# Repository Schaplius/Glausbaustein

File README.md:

# Glausbaustein
Einfache glasbausteinlampe mit steuerbaren leds und einem 3D-gedrucktem Gehäuse

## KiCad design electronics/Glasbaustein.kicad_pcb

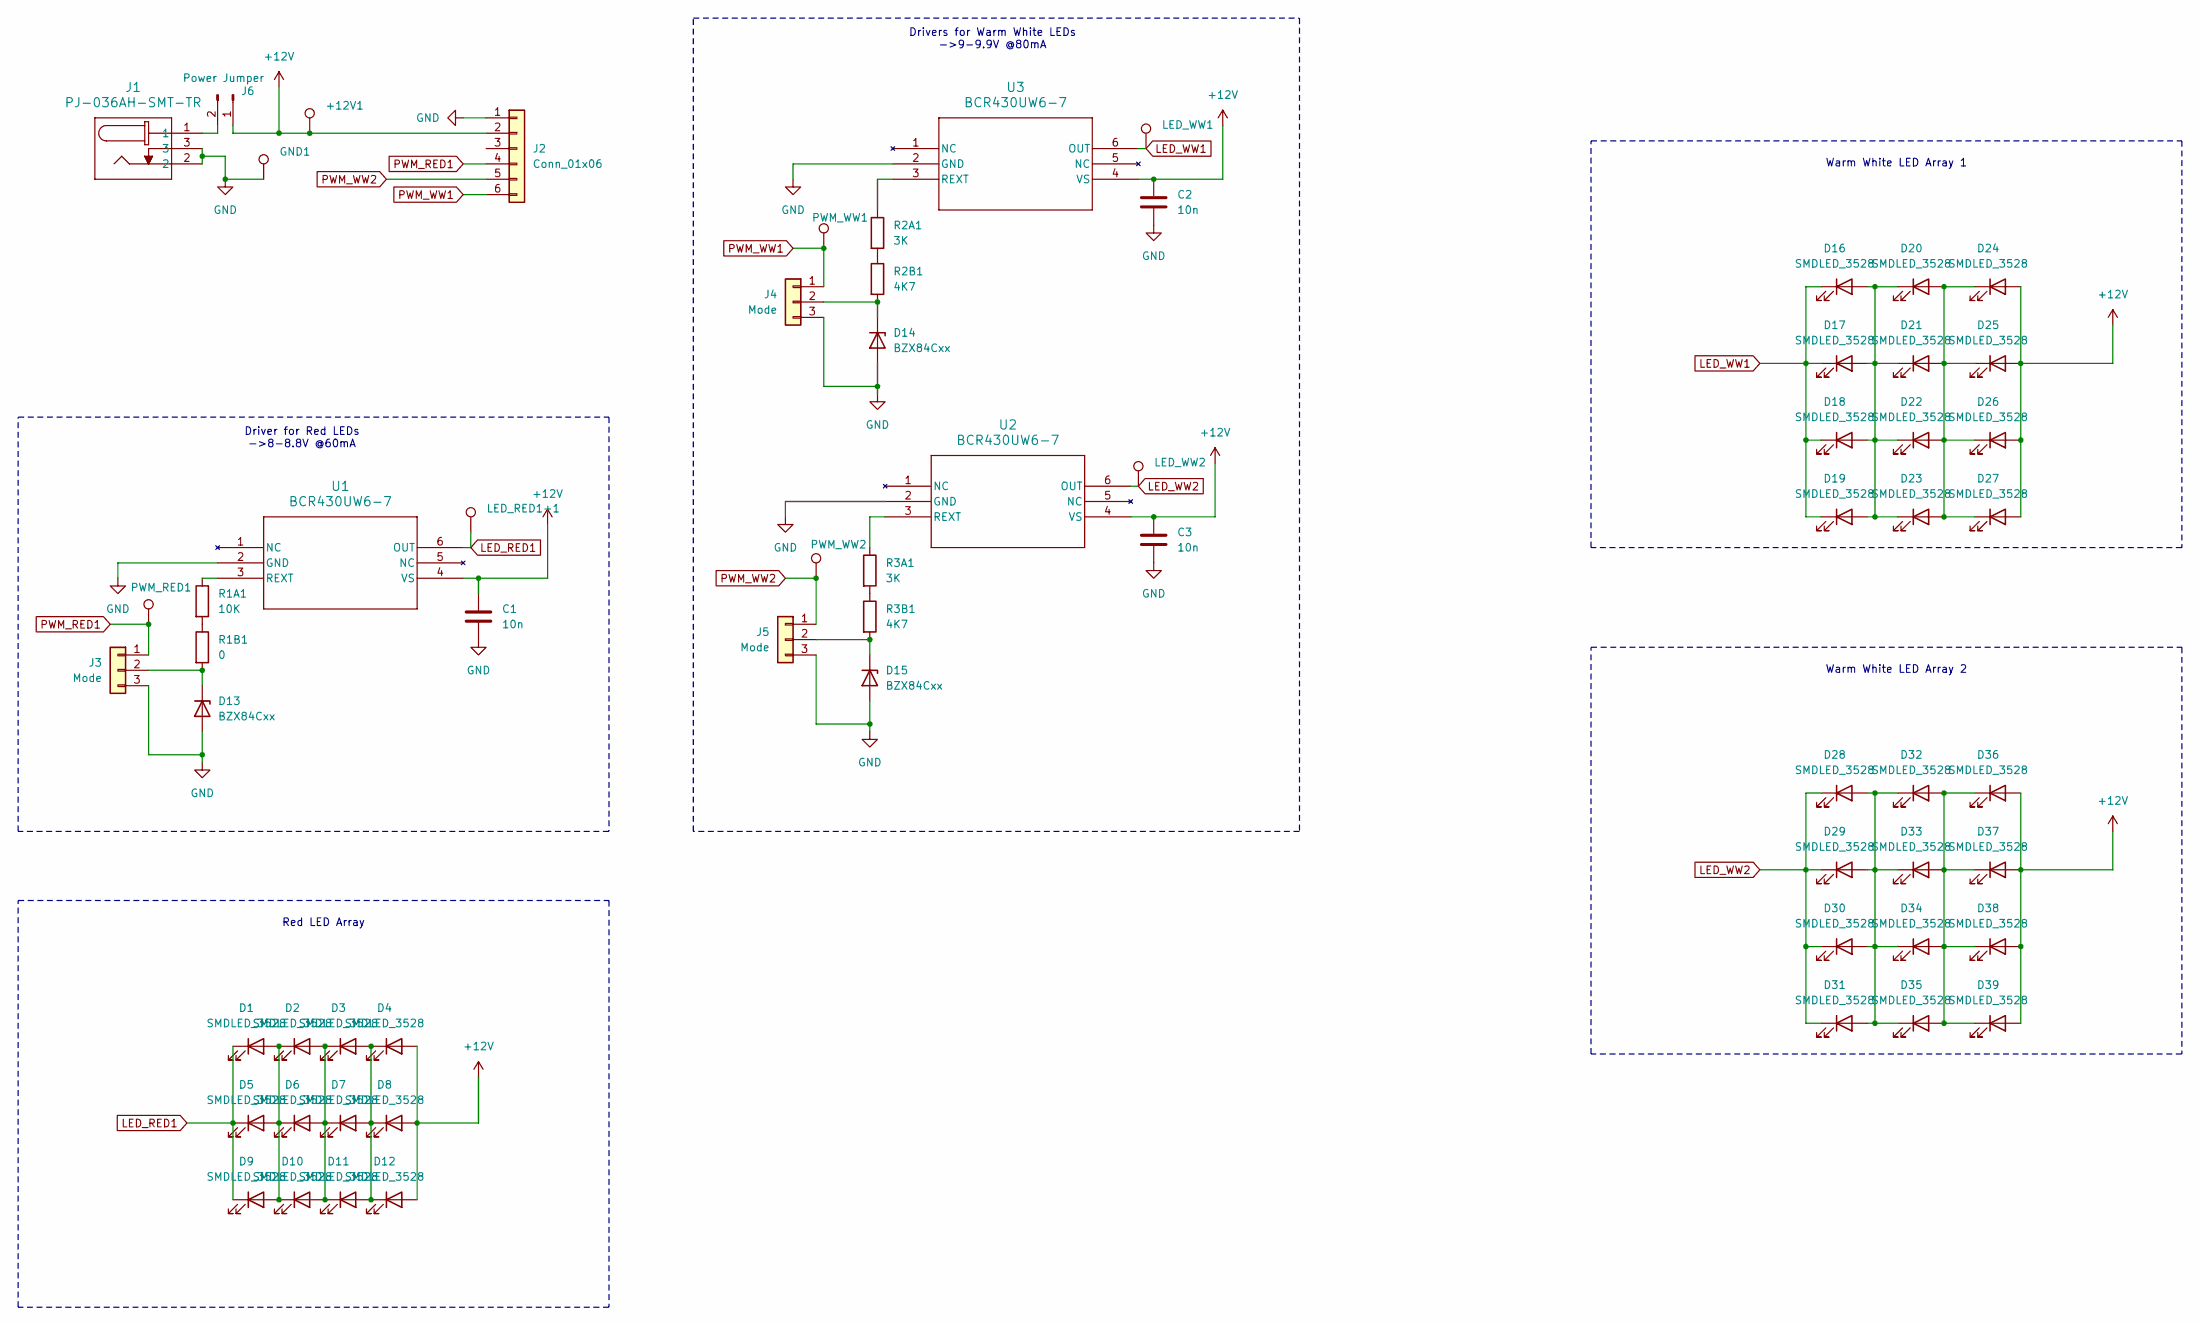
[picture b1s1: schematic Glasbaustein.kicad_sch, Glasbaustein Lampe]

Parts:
+12V1: TestPoint_Pad_D1.5mm
C1, C2, C3: 10n; C_1206_3216Metric_Pad1.33x1.80mm_HandSolder
D1, D2, D3, D4, D5, D6, D7, D8, D9, D10, D11, D12, D16, D17, D18, D19, D20, D21, D22, D23, D24, D25, D26, D27, D28, D29, D30, D31, D32, D33, D34, D35, D36, D37, D38, D39: SMDLED_3528; LED_PLCC_2835_Handsoldering
D13, D14, D15: BZX84Cxx; SOT-23
GND1: TestPoint_Pad_D1.5mm
J1: PJ-036AH-SMT-TR; CONN3_PJ-036AH_CUD
J2: Conn_01x06; PinHeader_1x06_P2.54mm_Vertical
J3, J4, J5: Mode; PinHeader_1x03_P2.54mm_Vertical
J6: Power Jumper; PinHeader_1x02_P2.54mm_Vertical
LED_RED1+1: TestPoint_Pad_D1.5mm
LED_WW1, LED_WW2: TestPoint_Pad_D1.5mm
PWM_RED1: TestPoint_Pad_D1.5mm
PWM_WW1, PWM_WW2: TestPoint_Pad_D1.5mm
R1A1: 10K; C_0603_1608Metric_Pad1.08x0.95mm_HandSolder
R1B1: 0; C_0603_1608Metric_Pad1.08x0.95mm_HandSolder
R2A1, R3A1: 3K; R_0603_1608Metric
R2B1, R3B1: 4K7; C_0603_1608Metric_Pad1.08x0.95mm_HandSolder
U1, U2, U3: BCR430UW6-7; BCR430UW6-7_DIO

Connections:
+12V: +12V1.1, C1.1, C2.1, C3.1, D4.2 (A), D8.2 (A), D12.2 (A), D24.2 (A), D25.2 (A), D26.2 (A), D27.2 (A), D36.2 (A), D37.2 (A), D38.2 (A), D39.2 (A), J2.2, J6.1, U1.4 (VS), U2.4 (VS), U3.4 (VS)
GND: C1.2, C2.2, C3.2, D13.1 (A), D14.1 (A), D15.1 (A), GND1.1, J1.2, J1.3, J2.1, J3.3, J4.3, J5.3, U1.2 (GND), U2.2 (GND), U3.2 (GND)
LED_RED1: D1.1 (K), D5.1 (K), D9.1 (K), LED_RED1+1.1, U1.6 (OUT)
LED_WW1: D16.1 (K), D17.1 (K), D18.1 (K), D19.1 (K), LED_WW1.1, U3.6 (OUT)
LED_WW2: D28.1 (K), D29.1 (K), D30.1 (K), D31.1 (K), LED_WW2.1, U2.6 (OUT)
unnamed: D1.2 (A), D2.1 (K), D5.2 (A), D6.1 (K), D9.2 (A), D10.1 (K)
unnamed: D2.2 (A), D3.1 (K), D6.2 (A), D7.1 (K), D10.2 (A), D11.1 (K)
unnamed: D3.2 (A), D4.1 (K), D7.2 (A), D8.1 (K), D11.2 (A), D12.1 (K)
unnamed: D13.3 (K), J3.2, R1B1.2
unnamed: D14.3 (K), J4.2, R2B1.2
unnamed: D15.3 (K), J5.2, R3B1.2
unnamed: D16.2 (A), D17.2 (A), D18.2 (A), D19.2 (A), D20.1 (K), D21.1 (K), D22.1 (K), D23.1 (K)
unnamed: D20.2 (A), D21.2 (A), D22.2 (A), D23.2 (A), D24.1 (K), D25.1 (K), D26.1 (K), D27.1 (K)
unnamed: D28.2 (A), D29.2 (A), D30.2 (A), D31.2 (A), D32.1 (K), D33.1 (K), D34.1 (K), D35.1 (K)
unnamed: D32.2 (A), D33.2 (A), D34.2 (A), D35.2 (A), D36.1 (K), D37.1 (K), D38.1 (K), D39.1 (K)
unnamed: J1.1, J6.2
unnamed: R1A1.2, R1B1.1
unnamed: R2A1.2, R2B1.1
unnamed: R3A1.2, R3B1.1
unnamed: R1A1.1, U1.3 (REXT)
unnamed: R3A1.1, U2.3 (REXT)
unnamed: R2A1.1, U3.3 (REXT)
PWM_RED1: J2.4, J3.1, PWM_RED1.1
PWM_WW1: J2.6, J4.1, PWM_WW1.1
PWM_WW2: J2.5, J5.1, PWM_WW2.1

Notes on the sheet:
Driver for Red LEDs ->8-8.8V @60mA
Drivers for Warm White LEDs ->9-9.9V @80mA
Warm White LED Array 2
Warm White LED Array 1
Red LED Array

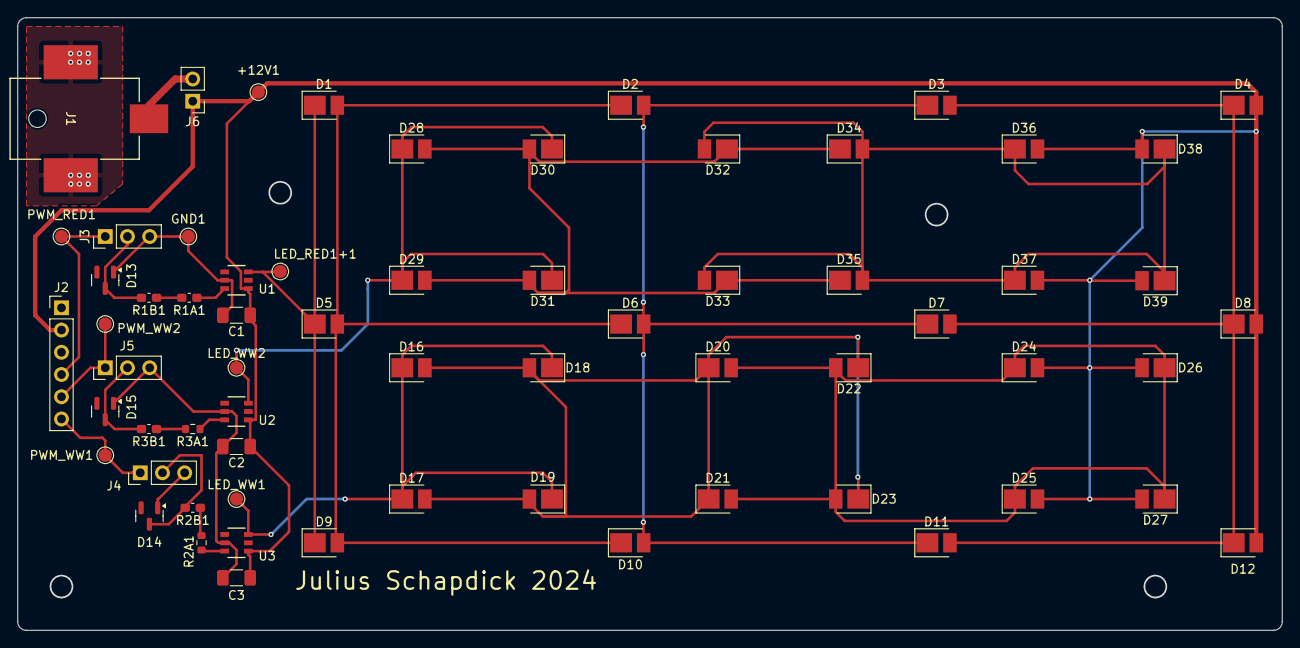
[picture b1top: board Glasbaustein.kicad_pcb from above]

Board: 2 copper layers, 144.5 x 70.0 mm, 65 parts (0 on the bottom side), 25 nets.

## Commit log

2025-06-19 uploaded first version to git
